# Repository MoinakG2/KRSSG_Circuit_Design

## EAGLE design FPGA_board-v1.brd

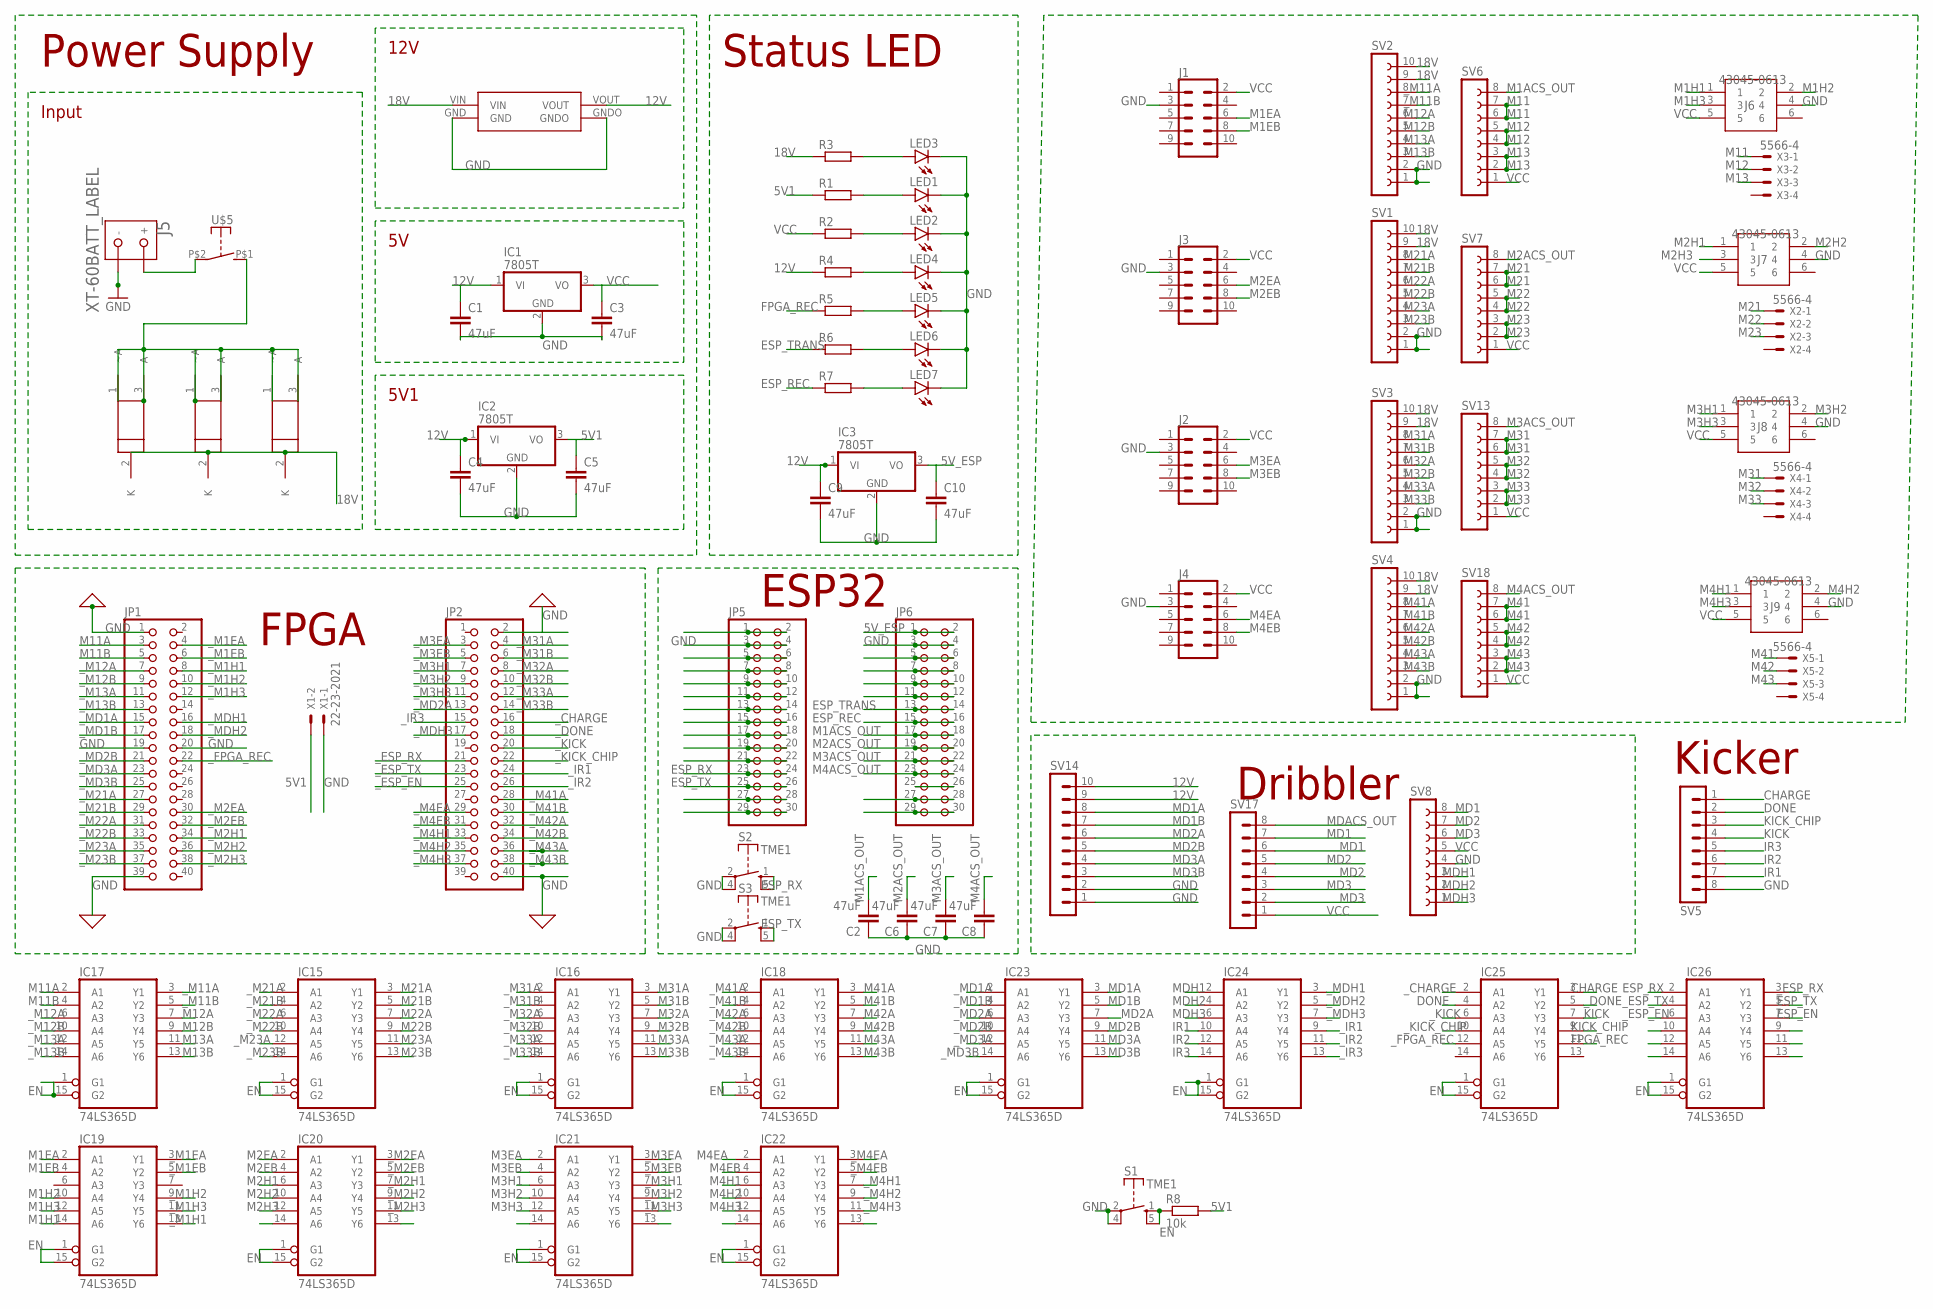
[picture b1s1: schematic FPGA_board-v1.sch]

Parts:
C1, C2, C3, C4, C5, C6, C7, C8, C9, C10: 47uF; C1206
IC1, IC2, IC3: 7805T; TO220H
IC15, IC16, IC17, IC18, IC19, IC20, IC21, IC22, IC23, IC24, IC25, IC26: 74LS365D; SO16
J1, J2, J3, J4: CONN_05X2SHD_LOCK; 2X5-SHROUDED_LOCK
J5: XT-60BATT_LABEL; XT-60
J6, J7, J8, J9: 43045-0613
JP1, JP2: PINHD-2X20; 2X20
JP5, JP6: PINHD-2X15; 2X15
LED1, LED2, LED3, LED4, LED5, LED6, LED7: LEDSMT1206; 1206
R1, R2, R3, R4, R5, R6, R7: R-EU_R1206; R1206
R8: 10k; 0204/7
S1, S2, S3: TME1
SV1, SV2, SV3, SV4: FE10-1; FE10
SV5, SV17: MA08-1
SV6, SV7, SV8, SV13, SV18: FE08-1; FE08
SV14: MA10-1
U1, U2, U3: LP38690DT-3.3; TO228P1042X238-3N
U$4: BUCK
U$5: SWITCH_DA10; DA10
X1: 22-23-2021
X2, X3, X4, X5: 5566-4

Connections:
5V1: C5.1, IC2.3 (VO), R1.1, R8.2, X1.2
5V_ESP: C10.1, IC3.3 (VO), JP6.1, JP6.2
12V: C1.1, C4.1, C9.1, IC1.1 (VI), IC2.1 (VI), IC3.1 (VI), R4.1, SV14.9, SV14.10, U$4.VOUT
18V: R3.1, SV1.9, SV1.10, SV2.9, SV2.10, SV3.9, SV3.10, SV4.9, SV4.10, U1.2 (K), U2.2 (K), U3.2 (K), U$4.VIN
CHARGE: IC25.3 (Y1), SV5.1
DONE: IC25.4 (A2), SV5.2
EN: IC15.1 (G1), IC15.15 (G2), IC16.1 (G1), IC16.15 (G2), IC17.1 (G1), IC17.15 (G2), IC18.1 (G1), IC18.15 (G2), IC19.1 (G1), IC19.15 (G2), IC20.1 (G1), IC20.15 (G2), IC21.1 (G1), IC21.15 (G2), IC22.1 (G1), IC22.15 (G2), IC23.1 (G1), IC23.15 (G2), IC24.1 (G1), IC24.15 (G2), IC25.1 (G1), IC25.15 (G2), IC26.1 (G1), IC26.15 (G2), R8.1, S1.1 (S), S1.5 (S)
ESP_EN: IC26.7 (Y3)
ESP_REC: JP6.15, JP6.16, R7.1
ESP_RX: IC26.2 (A1), JP5.23, JP5.24, S2.1 (S), S2.5 (S)
ESP_TRANS: JP6.13, JP6.14, R6.1
ESP_TX: IC26.5 (Y2), JP5.25, JP5.26, S3.1 (S), S3.5 (S)
FPGA_REC: IC25.11 (Y5), R5.1
GND: C1.2, C2.1, C3.2, C4.2, C5.2, C6.1, C7.1, C8.1, C9.2, C10.2, IC1.2 (GND), IC2.2 (GND), IC3.2 (GND), IC15.8 (GND), IC16.8 (GND), IC17.8 (GND), IC18.8 (GND), IC19.8 (GND), IC20.8 (GND), IC21.8 (GND), IC22.8 (GND), IC23.8 (GND), IC24.8 (GND), IC25.8 (GND), IC26.8 (GND), J1.3, J2.3, J3.3, J4.3, J5.GND (-), J6.4, J7.4, J8.4, J9.4, JP1.1, JP1.19, JP1.20, JP1.39, JP2.2, JP2.40, JP5.3, JP5.4, JP6.3, JP6.4, LED1.C, LED2.C, LED3.C, LED4.C, LED5.C, LED6.C, LED7.C, S1.2, S1.4, S2.2, S2.4, S3.2, S3.4, SV1.1, SV1.2, SV2.1, SV2.2, SV3.1, SV3.2, SV4.1, SV4.2, SV5.8, SV8.4, SV14.1, SV14.2, U$4.GND, U$4.GNDO, X1.1
INPUT: U1.1 (~A), U1.3 (A), U2.1 (~A), U2.3 (A), U3.1 (~A), U3.3 (A), U$5.P$1 (S)
IR1: IC24.10 (A4), SV5.7
IR2: IC24.12 (A5), SV5.6
IR3: IC24.14 (A6), SV5.5
KICK: IC25.7 (Y3), SV5.4
KICK_CHIP: IC25.9 (Y4), SV5.3
M1ACS_OUT: C2.2, JP6.17, JP6.18, SV6.8
M1EA: IC19.2 (A1), J1.6
M1EB: IC19.4 (A2), J1.8
M1H1: IC19.14 (A6), J6.1
M1H2: IC19.10 (A4), J6.2
M1H3: IC19.12 (A5), J6.3
M2ACS_OUT: C6.2, JP6.19, JP6.20, SV7.8
M2EA: IC20.2 (A1), J3.6
M2EB: IC20.4 (A2), J3.8
M2H1: IC20.6 (A3), J7.1
M2H2: IC20.10 (A4), J7.2
M2H3: IC20.12 (A5), J7.3
M3ACS_OUT: C7.2, JP6.21, JP6.22, SV13.8
M3EA: IC21.2 (A1), J2.6
M3EB: IC21.4 (A2), J2.8
M3H1: IC21.6 (A3), J8.1
M3H2: IC21.10 (A4), J8.2
M3H3: IC21.12 (A5), J8.3
M4ACS_OUT: C8.2, JP6.23, JP6.24, SV18.8
M4EA: IC22.2 (A1), J4.6
M4EB: IC22.4 (A2), J4.8
M4H1: IC22.6 (A3), J9.1
M4H2: IC22.10 (A4), J9.2
M4H3: IC22.12 (A5), J9.3
M11: SV6.6, SV6.7, X3.1
M11A: IC17.2 (A1), JP1.3
M11B: IC17.4 (A2), JP1.5
M12: SV6.4, SV6.5, X3.2
M12A: IC17.7 (Y3), SV2.6
M12B: IC17.9 (Y4), SV2.5
M13: SV6.2, SV6.3, X3.3
M13A: IC17.11 (Y5), SV2.4
M13B: IC17.13 (Y6), SV2.3
M21: SV7.6, SV7.7, X2.1
M21A: IC15.3 (Y1), SV1.8
M21B: IC15.5 (Y2), SV1.7
M22: SV7.4, SV7.5, X2.2
M22A: IC15.7 (Y3), SV1.6
M22B: IC15.9 (Y4), SV1.5
M23: SV7.2, SV7.3, X2.3
M23A: IC15.11 (Y5), SV1.4
M23B: IC15.13 (Y6), SV1.3
M31: SV13.6, SV13.7, X4.1
M31A: IC16.3 (Y1), SV3.8
M31B: IC16.5 (Y2), SV3.7
M32: SV13.4, SV13.5, X4.2
M32A: IC16.7 (Y3), SV3.6
M32B: IC16.9 (Y4), SV3.5
M33: SV13.2, SV13.3, X4.3
M33A: IC16.11 (Y5), SV3.4
M33B: IC16.13 (Y6), SV3.3
M41: SV18.6, SV18.7, X5.1
M41A: IC18.3 (Y1), SV4.8
M41B: IC18.5 (Y2), SV4.7
M42: SV18.4, SV18.5, X5.2
M42A: IC18.7 (Y3), SV4.6
M42B: IC18.9 (Y4), SV4.5
M43: SV18.2, SV18.3, X5.3
M43A: IC18.11 (Y5), SV4.4
M43B: IC18.13 (Y6), SV4.3
MD1: SV8.8, SV17.6, SV17.7
MD1A: IC23.3 (Y1), SV14.8
MD1B: IC23.5 (Y2), SV14.7
MD2: SV8.7, SV17.4, SV17.5
MD2A: IC23.7 (Y3), SV14.6
MD2B: IC23.9 (Y4), SV14.5
MD3: SV8.6, SV17.2, SV17.3
MD3A: IC23.11 (Y5), SV14.4
MD3B: IC23.13 (Y6), SV14.3
MDACS_OUT: SV17.8
MDH1: IC24.2 (A1), SV8.3
MDH2: IC24.4 (A2), SV8.2
MDH3: IC24.6 (A3), SV8.1
unnamed: JP5.1, JP5.2
unnamed: LED1.A, R1.2
unnamed: JP5.5, JP5.6
unnamed: LED2.A, R2.2
unnamed: JP5.7, JP5.8
unnamed: JP5.9, JP5.10
unnamed: LED3.A, R3.2
unnamed: JP5.11, JP5.12
unnamed: JP5.13, JP5.14
unnamed: LED4.A, R4.2
unnamed: JP5.15, JP5.16
unnamed: JP5.17, JP5.18
unnamed: LED5.A, R5.2
unnamed: JP5.19, JP5.20
unnamed: JP5.21, JP5.22
unnamed: LED6.A, R6.2
unnamed: LED7.A, R7.2
unnamed: JP5.27, JP5.28
unnamed: JP5.29, JP5.30
unnamed: JP6.5, JP6.6
unnamed: JP6.7, JP6.8
unnamed: JP6.9, JP6.10
unnamed: JP6.11, JP6.12
unnamed: JP6.27, JP6.28
unnamed: JP6.29, JP6.30
unnamed: JP6.25, JP6.26
SUPP: J5.BATT (+), U$5.P$2
VCC: C3.1, IC1.3 (VO), IC15.16 (VCC), IC16.16 (VCC), IC17.16 (VCC), IC18.16 (VCC), IC19.16 (VCC), IC20.16 (VCC), IC21.16 (VCC), IC22.16 (VCC), IC23.16 (VCC), IC24.16 (VCC), IC25.16 (VCC), IC26.16 (VCC), J1.2, J2.2, J3.2, J4.2, J6.5, J7.5, J8.5, J9.5, R2.1, SV6.1, SV7.1, SV8.5, SV13.1, SV17.1, SV18.1
_CHARGE: IC25.2 (A1), JP2.16
_DONE: IC25.5 (Y2), JP2.18
_ESP_EN: IC26.6 (A3), JP2.25
_ESP_RX: IC26.3 (Y1), JP2.21
_ESP_TX: IC26.4 (A2), JP2.23
_FPGA_REC: IC25.12 (A5), JP1.22
_IR1: IC24.9 (Y4), JP2.24
_IR2: IC24.11 (Y5), JP2.26
_IR3: IC24.13 (Y6), JP2.15
_KICK: IC25.6 (A3), JP2.20
_KICK_CHIP: IC25.10 (A4), JP2.22
_M1EA: IC19.3 (Y1), JP1.4
_M1EB: IC19.5 (Y2), JP1.6
_M1H1: IC19.13 (Y6), JP1.8
_M1H2: IC19.9 (Y4), JP1.10
_M1H3: IC19.11 (Y5), JP1.12
_M2EA: IC20.3 (Y1), JP1.30
_M2EB: IC20.5 (Y2), JP1.32
_M2H1: IC20.7 (Y3), JP1.34
_M2H2: IC20.9 (Y4), JP1.36
_M2H3: IC20.11 (Y5), JP1.38
_M3EA: IC21.3 (Y1), JP2.3
_M3EB: IC21.5 (Y2), JP2.5
_M3H1: IC21.7 (Y3), JP2.7
_M3H2: IC21.9 (Y4), JP2.9
_M3H3: IC21.11 (Y5), JP2.11
_M4EA: IC22.3 (Y1), JP2.29
_M4EB: IC22.5 (Y2), JP2.31
_M4H1: IC22.7 (Y3), JP2.33
_M4H2: IC22.9 (Y4), JP2.35
_M4H3: IC22.11 (Y5), JP2.37
_M11A: IC17.3 (Y1), SV2.8
_M11B: IC17.5 (Y2), SV2.7
_M12A: IC17.6 (A3), JP1.7
_M12B: IC17.10 (A4), JP1.9
_M13A: IC17.12 (A5), JP1.11
_M13B: IC17.14 (A6), JP1.13
_M21A: IC15.2 (A1), JP1.27
_M21B: IC15.4 (A2), JP1.29
_M22A: IC15.6 (A3), JP1.31
_M22B: IC15.10 (A4), JP1.33
_M23A: IC15.12 (A5), JP1.35
_M23B: IC15.14 (A6), JP1.37
_M31A: IC16.2 (A1), JP2.4
_M31B: IC16.4 (A2), JP2.6
_M32A: IC16.6 (A3), JP2.8
_M32B: IC16.10 (A4), JP2.10
_M33A: IC16.12 (A5), JP2.12
_M33B: IC16.14 (A6), JP2.14
_M41A: IC18.2 (A1), JP2.28
_M41B: IC18.4 (A2), JP2.30
_M42A: IC18.6 (A3), JP2.32
_M42B: IC18.10 (A4), JP2.34
_M43A: IC18.12 (A5), JP2.36
_M43B: IC18.14 (A6), JP2.38
_MD1A: IC23.2 (A1), JP1.15
_MD1B: IC23.4 (A2), JP1.17
_MD2A: IC23.6 (A3), JP2.13
_MD2B: IC23.10 (A4), JP1.21
_MD3A: IC23.12 (A5), JP1.23
_MD3B: IC23.14 (A6), JP1.25
_MDH1: IC24.3 (Y1), JP1.16
_MDH2: IC24.5 (Y2), JP1.18
_MDH3: IC24.7 (Y3), JP2.17

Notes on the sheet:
Power Supply
FPGA
Status LED
Dribbler
Kicker
ESP32
Input
12V
5V1

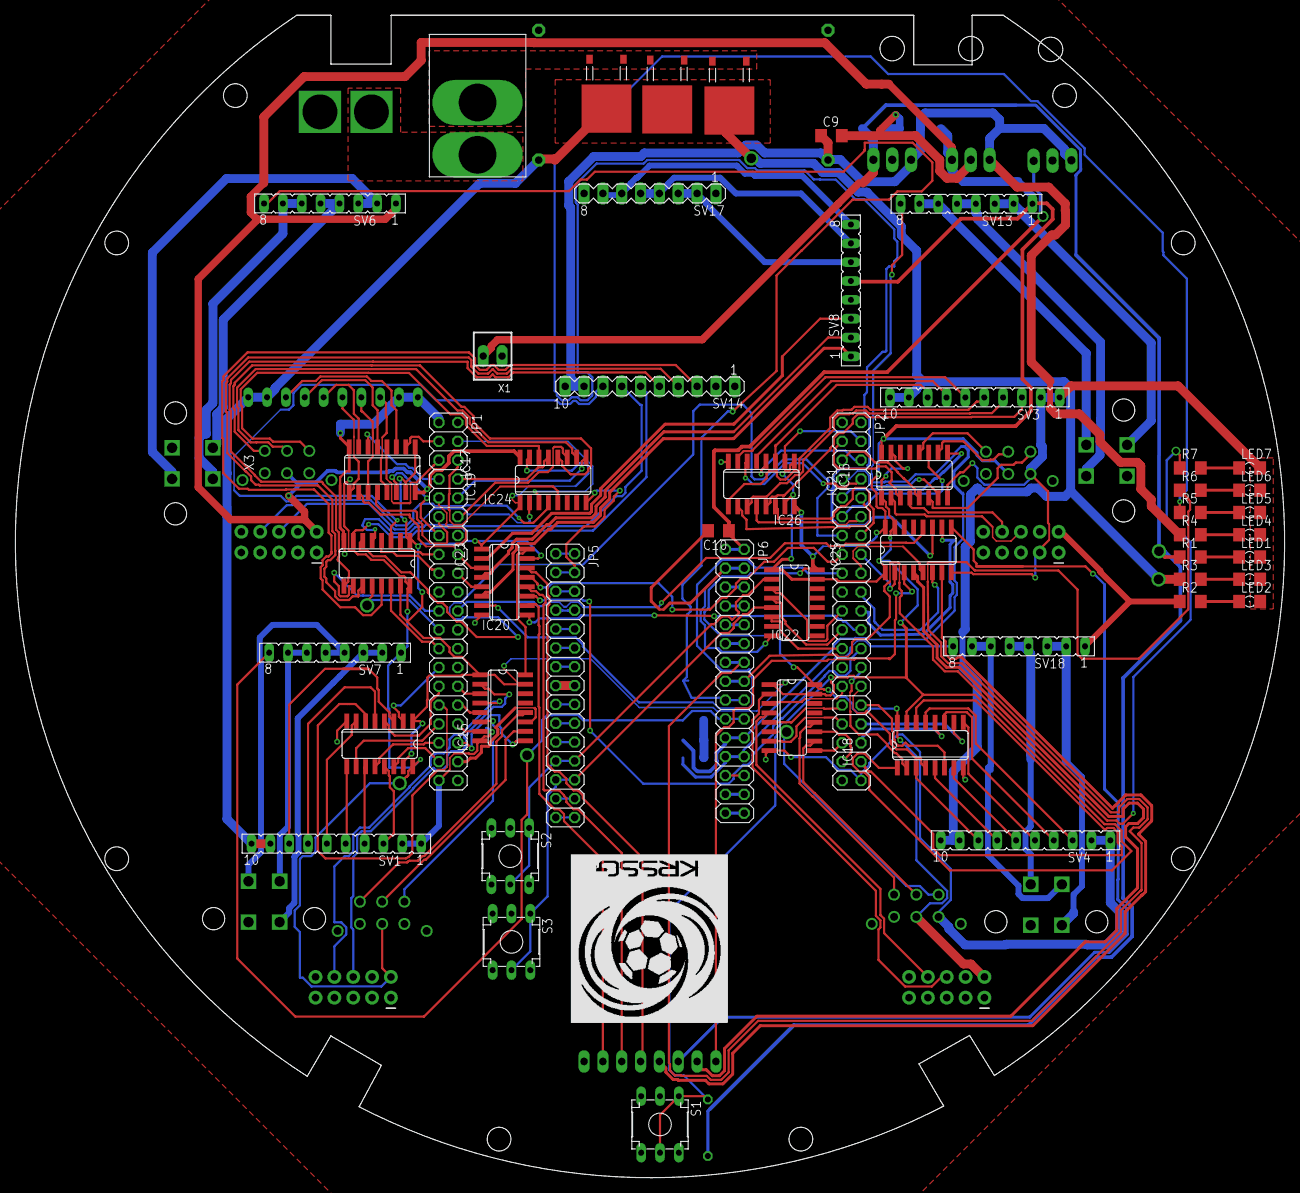
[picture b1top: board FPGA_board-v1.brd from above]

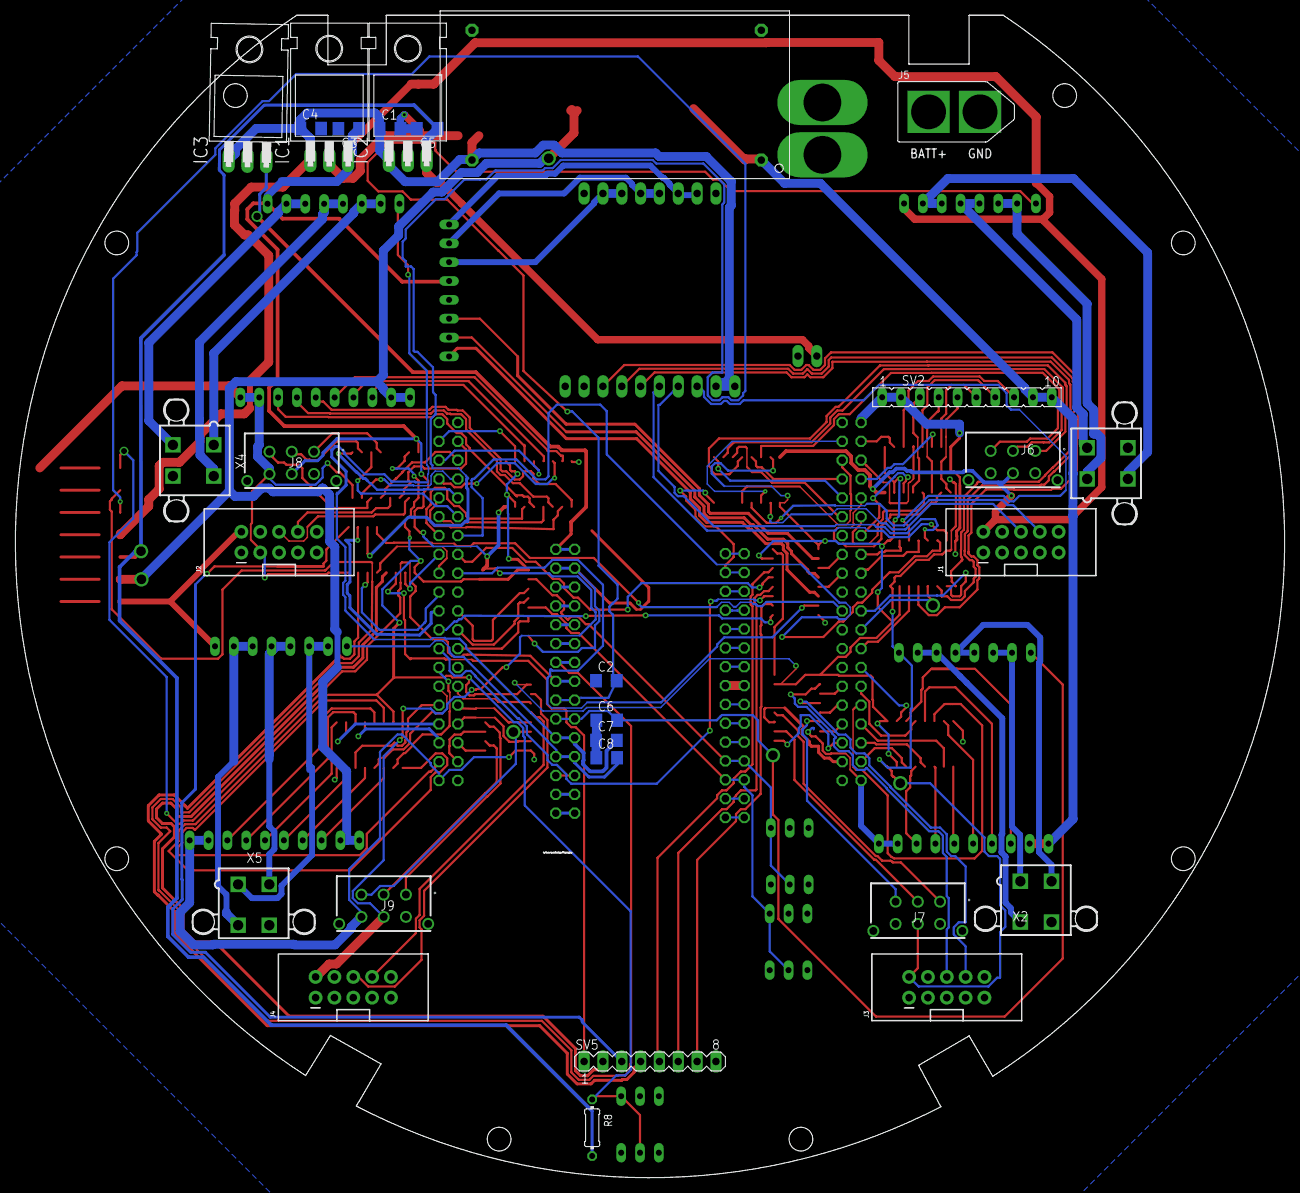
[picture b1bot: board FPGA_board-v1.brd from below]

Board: 2 copper layers, 171.1 x 156.7 mm, 79 parts (28 on the bottom side), 183 nets.

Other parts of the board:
U$1: LOGO3

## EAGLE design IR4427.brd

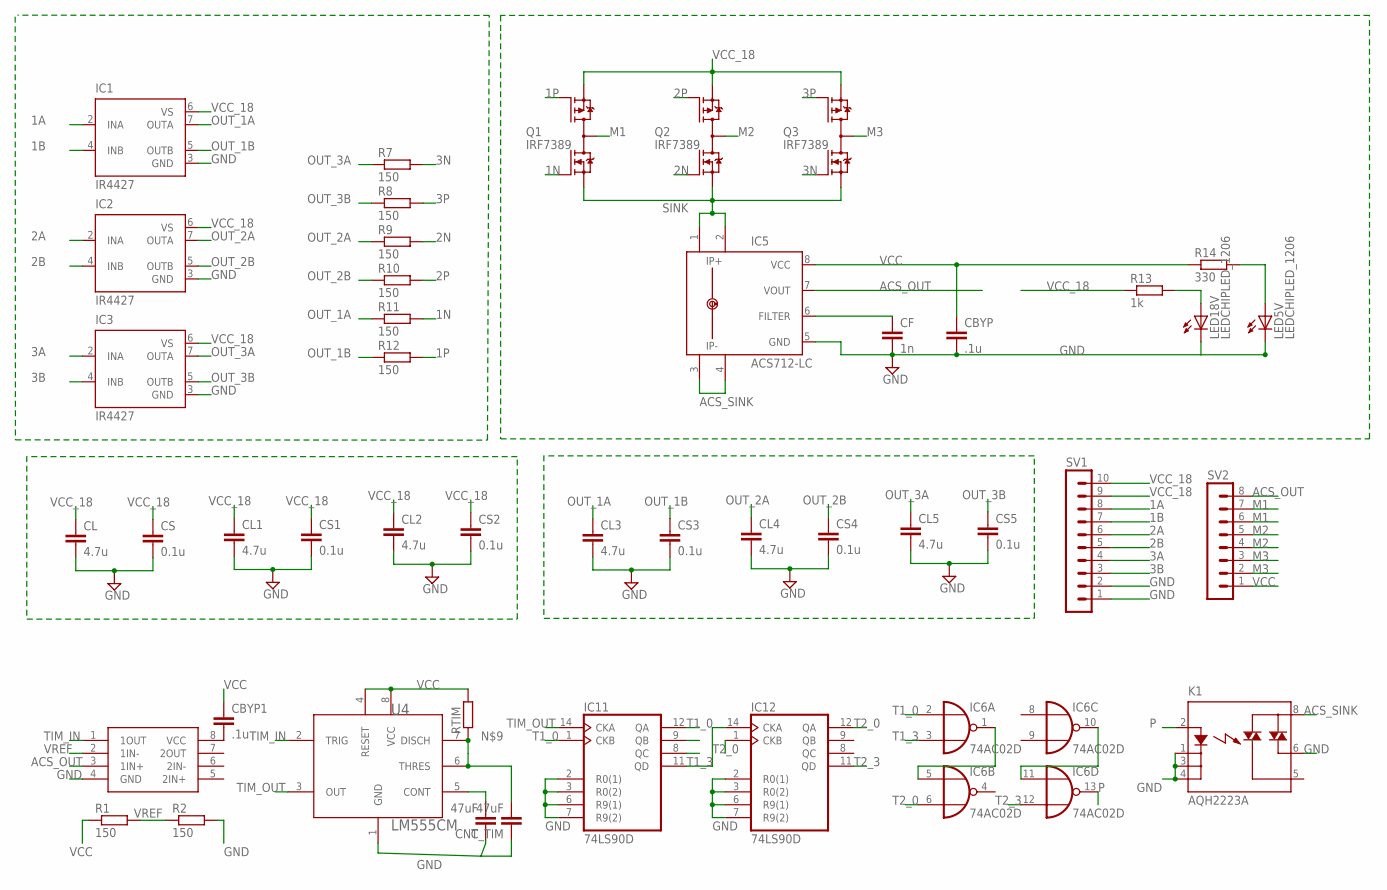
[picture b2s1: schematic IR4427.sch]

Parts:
CBYP, CBYP1: .1u; C1206
CF: 1n; C1206
CL, CL1, CL2, CL3, CL4, CL5: 4.7u; C1206
CNT: 47uF; C1206
CS, CS1, CS2, CS3, CS4, CS5: 0.1u; C1206
C_TIM: 47uF; C1206
IC1, IC2, IC3: IR4427; DIL08
IC5: ACS712-LC; SOIC8
IC6: 74AC02D; SO14
IC11, IC12: 74LS90D; SO14
K1: AQH2223A; DIL07SMD
LED5V, LED18V: LEDCHIPLED_1206; CHIPLED_1206
Q1, Q2, Q3: IRF7389; SO08-IRF
R1, R2, R7, R8, R9, R10, R11, R12: 150; R1206
R13: 1k; R1206
R14: 330; R1206
RTIM: R-EU_R1206; R1206
SV1: MA10-1
SV2: MA08-1
U1: LM293D; 8-SOIC
U4: LM555CM; SOIC-8N

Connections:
1A: IC1.2 (INA), SV1.8
1B: IC1.4 (INB), SV1.7
1N: Q1.2 (N-G), R11.2
1P: Q1.4 (P-G), R12.2
2A: IC2.2 (INA), SV1.6
2B: IC2.4 (INB), SV1.5
2N: Q2.2 (N-G), R9.2
2P: Q2.4 (P-G), R10.2
3A: IC3.2 (INA), SV1.4
3B: IC3.4 (INB), SV1.3
3N: Q3.2 (N-G), R7.2
3P: Q3.4 (P-G), R8.2
ACS_OUT: IC5.7 (VOUT), SV2.8, U1.3 (1IN+)
ACS_SINK: IC5.3 (IP-), IC5.4 (IP-1), K1.8 (DS1)
GND: CBYP.2, CF.2, CL.2, CL1.2, CL2.2, CL3.2, CL4.2, CL5.2, CNT.1, CS.2, CS1.2, CS2.2, CS3.2, CS4.2, CS5.2, C_TIM.1, IC1.3 (GND), IC2.3 (GND), IC3.3 (GND), IC5.5 (GND), IC6.7 (GND), IC11.2 (R0(1)), IC11.3 (R0(2)), IC11.6 (R9(1)), IC11.7 (R9(2)), IC11.10 (GND), IC12.2 (R0(1)), IC12.3 (R0(2)), IC12.6 (R9(1)), IC12.7 (R9(2)), IC12.10 (GND), K1.1 (K), K1.3 (K1), K1.4 (K2), K1.6 (DS3), LED5V.C, LED18V.C, R2.2, SV1.1, SV1.2, U1.4 (GND), U4.1 (GND)
M1: Q1.5 (D), Q1.6 (D), Q1.7 (D), Q1.8 (D), SV2.6, SV2.7
M2: Q2.5 (D), Q2.6 (D), Q2.7 (D), Q2.8 (D), SV2.4, SV2.5
M3: Q3.5 (D), Q3.6 (D), Q3.7 (D), Q3.8 (D), SV2.2, SV2.3
unnamed: LED18V.A, R13.2
unnamed: CF.1, IC5.6 (FILTER)
unnamed: LED5V.A, R14.2
unnamed: IC6.1 (O), IC6.5 (I0)
unnamed: RTIM.1, U4.7 (DISCH)
unnamed: IC6.10 (O), IC6.11 (I0)
unnamed: CBYP1.2, U1.8 (VCC)
unnamed: CNT.2, U4.5 (CONT)
unnamed: C_TIM.2, U4.6 (THRES)
OUT_1A: CL3.1, IC1.7 (OUTA), R11.1
OUT_1B: CS3.1, IC1.5 (OUTB), R12.1
OUT_2A: CL4.1, IC2.7 (OUTA), R9.1
OUT_2B: CS4.1, IC2.5 (OUTB), R10.1
OUT_3A: CL5.1, IC3.7 (OUTA), R7.1
OUT_3B: CS5.1, IC3.5 (OUTB), R8.1
P: IC6.13 (O), K1.2 (A)
SINK: IC5.1 (IP+), IC5.2 (IP+1), Q1.1 (N-S), Q2.1 (N-S), Q3.1 (N-S)
T1_0: IC6.2 (I0), IC11.1 (CKB), IC11.12 (QA)
T1_3: IC6.3 (I1), IC11.11 (QD), IC12.14 (CKA)
T2_0: IC6.6 (I1), IC12.1 (CKB), IC12.12 (QA)
T2_3: IC6.12 (I1), IC12.11 (QD)
TIM_IN: U1.1 (1OUT), U4.2 (TRIG)
TIM_OUT: IC11.14 (CKA), U4.3 (OUT)
VCC: CBYP.1, CBYP1.1, IC5.8 (VCC), IC6.14 (VCC), IC11.5 (VCC), IC12.5 (VCC), R1.1, R14.1, RTIM.2, SV2.1, U4.4 (RESET), U4.8 (VCC)
VCC_18: CL.1, CL1.1, CL2.1, CS.1, CS1.1, CS2.1, IC1.6 (VS), IC2.6 (VS), IC3.6 (VS), Q1.3 (P-S), Q2.3 (P-S), Q3.3 (P-S), R13.1, SV1.9, SV1.10
VREF: R1.2, R2.1, U1.2 (1IN-)

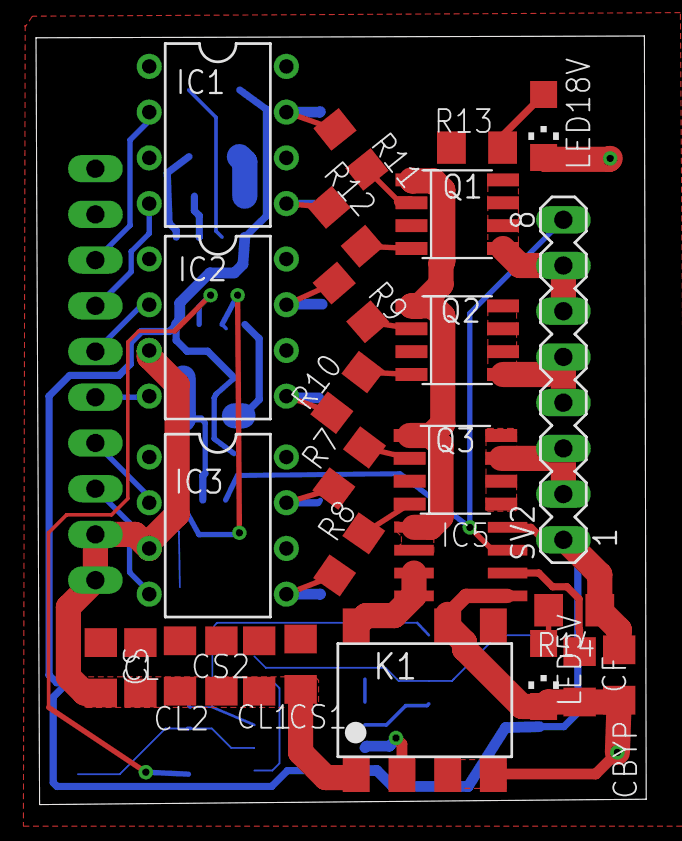
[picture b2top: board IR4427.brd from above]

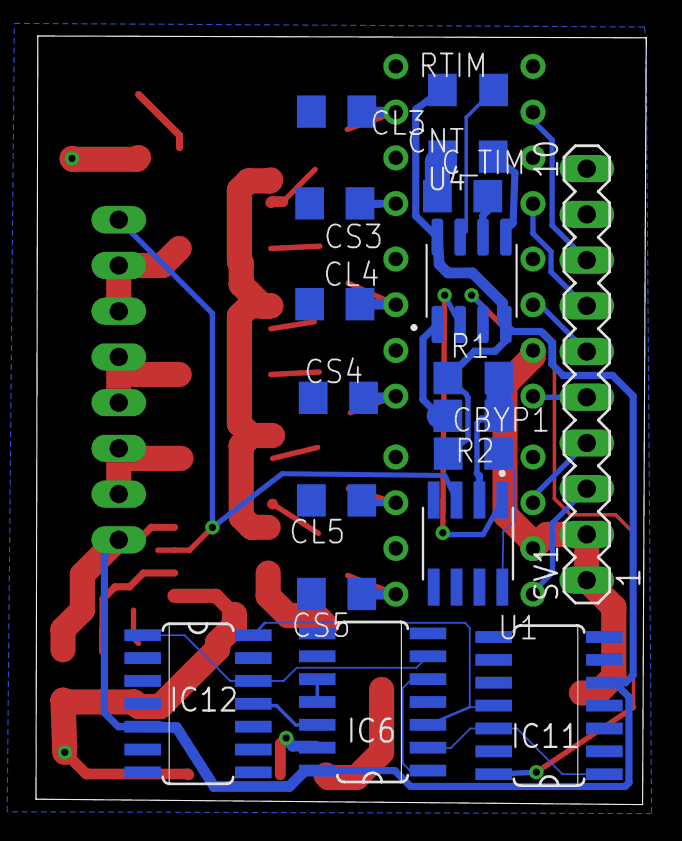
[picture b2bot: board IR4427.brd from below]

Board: 2 copper layers, 33.9 x 42.7 mm, 45 parts (18 on the bottom side), 44 nets.

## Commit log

2019-06-24 Create Ball detector
2019-06-24 Create Discharging Circuit
2019-06-24 Create Charging circuit for capacitor
2021-11-26 Added latest versions of main board

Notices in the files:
parts and their libraries:
SparkFun-Connectors: Licensing: Creative Commons ShareAlike 4.0 International - https://creativecommons.org/licenses/by-sa/4.0
